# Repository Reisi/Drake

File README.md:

# Drake

The Drake hardware is a multi-purpose PCB which can be used to build a wireless dropper post actuator or a rear light.

## Actuator

### Features

- Bluetooth connectivity for remote control and configuration.
- I2C connectivity for control, configuration and sensor readings.
- construction files for Fox Transfer dropper posts available

## Light

### Features

- two configurations with either 16 or 44 WS2812 LEDs
- 8 configurable modes
- configurable LED pattern
- ability to control a dropper actuator over a FFC (using I2C)

## Firmware

Drake is part of The Helen Project. The source code and compiled firmware files are available [here](https://github.com/Reisi/The_Helen_Project/tree/master/Firmware/Helen/boards/Drake_10)

## License

This project is licensed under the BSD-2-clause License - see the [license.txt](license.txt) file for details

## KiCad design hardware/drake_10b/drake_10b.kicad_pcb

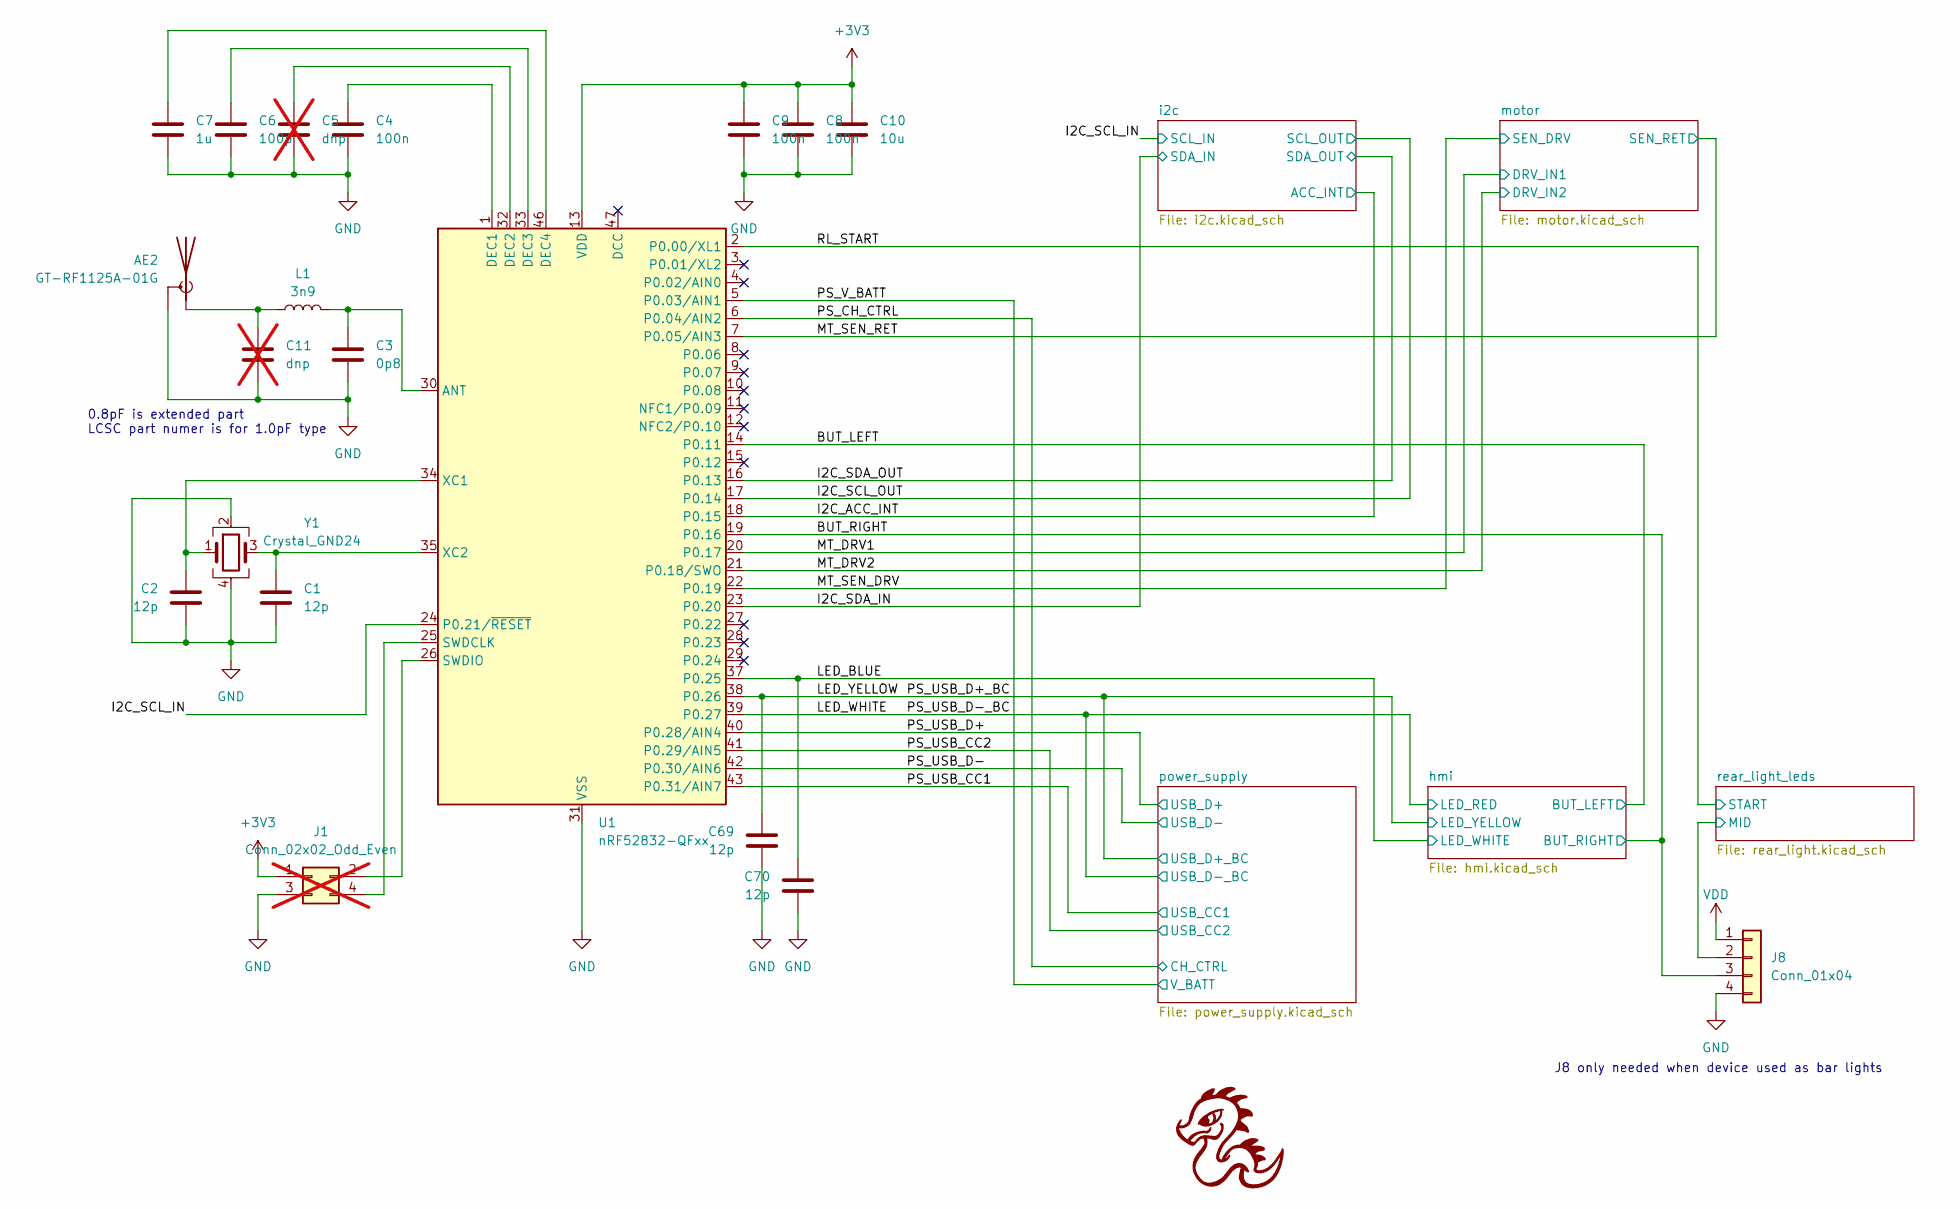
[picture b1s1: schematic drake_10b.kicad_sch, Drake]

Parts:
AE2: GT-RF1125A-01G; U.FL_Hirose_U.FL-R-SMT-1_Vertical; JLC SMD
C1, C2, C69, C70: 12p; C_0402_1005Metric; JLC 0402
C3: 0p8; C_0402_1005Metric; JLC 0402
C4, C8, C9: 100n; C_0402_1005Metric; JLC 0402
C5, C11: dnp; C_0402_1005Metric; not fitted
C6: 100p; C_0402_1005Metric; JLC 0402
C7: 1u; C_0402_1005Metric; JLC 0402
C10: 10u; C_0603_1608Metric; JLC 0603
J1: Conn_02x02_Odd_Even; PinHeader_2x02_P1.27mm_Vertical; not fitted
J8: Conn_01x04; Jushuo_AFC01-S04FCC-00_1x04-1MP_P0.50_Horizontal; JLC SMD,P=0.5mm
L1: 3n9; L_0402_1005Metric; JLC 0402
U1: nRF52832-QFxx; QFN-48-1EP_6x6mm_P0.4mm_EP4.6x4.6mm; JLC QFN-48-EP(6x6)
Y1: Crystal_GND24; Crystal_SMD_2016-4Pin_2.0x1.6mm; JLC SMD2016-4P

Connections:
+3V3: C8.1, C9.1, C10.1, J1.1, U1.13 (VDD), U1.36 (VDD), U1.48 (VDD); also elsewhere on the board
/BUT_LEFT: U1.14 (P0.11); also elsewhere on the board
/BUT_RIGHT: J8.3, U1.19 (P0.16); also elsewhere on the board
/I2C_ACC_INT: U1.18 (P0.15); also elsewhere on the board
/I2C_SCL_IN: U1.24 (P0.21/~RESET); also elsewhere on the board
/I2C_SCL_OUT: U1.17 (P0.14); also elsewhere on the board
/I2C_SDA_IN: U1.23 (P0.20); also elsewhere on the board
/I2C_SDA_OUT: U1.16 (P0.13); also elsewhere on the board
/LED_BLUE: C70.1, U1.37 (P0.25); also elsewhere on the board
/LED_WHITE: U1.39 (P0.27); also elsewhere on the board
/LED_YELLOW: C69.1, U1.38 (P0.26); also elsewhere on the board
/MT_DRV1: U1.20 (P0.17); also elsewhere on the board
/MT_DRV2: U1.21 (P0.18/SWO); also elsewhere on the board
/MT_SEN_DRV: U1.22 (P0.19); also elsewhere on the board
/MT_SEN_RET: U1.7 (P0.05/AIN3); also elsewhere on the board
/PS_CH_CTRL: U1.6 (P0.04/AIN2); also elsewhere on the board
/PS_USB_CC1: U1.43 (P0.31/AIN7); also elsewhere on the board
/PS_USB_CC2: U1.41 (P0.29/AIN5); also elsewhere on the board
/PS_USB_D+: U1.40 (P0.28/AIN4); also elsewhere on the board
/PS_USB_D-: U1.42 (P0.30/AIN6); also elsewhere on the board
/PS_V_BATT: U1.5 (P0.03/AIN1); also elsewhere on the board
/RL_START: U1.2 (P0.00/XL1); also elsewhere on the board
/rear_light_leds/MID: J8.2; also elsewhere on the board
GND: AE2.2 (Shield), C1.2, C2.2, C3.2, C4.2, C5.2, C6.2, C7.2, C8.2, C9.2, C10.2, C11.2, C69.2, C70.2, J1.3, J8.4, U1.31 (VSS), U1.45 (VSS), U1.49 (VSS), Y1.2, Y1.4; also elsewhere on the board
unnamed: AE2.1 (A), C11.1, L1.1
unnamed: J1.2, U1.26 (SWDIO)
unnamed: J1.4, U1.25 (SWDCLK)
unnamed: C3.1, L1.2, U1.30 (ANT)
unnamed: C4.1, U1.1 (DEC1)
unnamed: C5.1, U1.32 (DEC2)
unnamed: C6.1, U1.33 (DEC3)
unnamed: C7.1, U1.46 (DEC4)
unnamed: C2.1, U1.34 (XC1), Y1.1
unnamed: C1.1, U1.35 (XC2), Y1.3
VDD: J8.1; also elsewhere on the board

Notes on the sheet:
J8 only needed when device used as bar lights
0.8pF is extended part LCSC part numer is for 1.0pF type

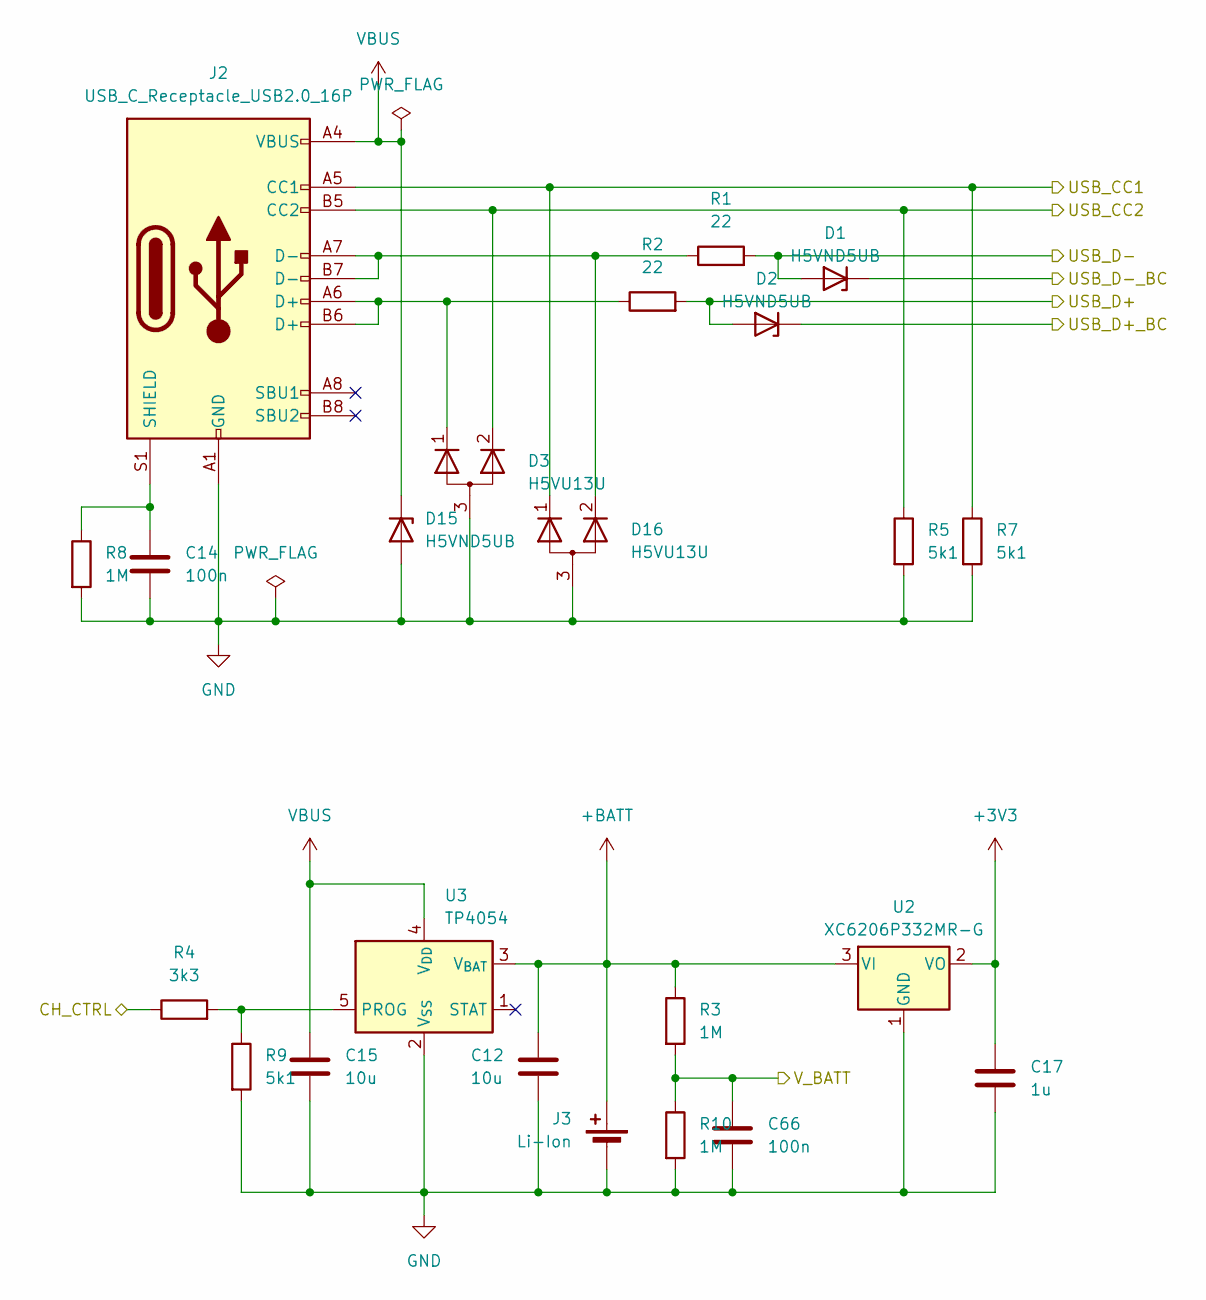
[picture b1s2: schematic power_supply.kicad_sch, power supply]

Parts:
C12, C15: 10u; C_0603_1608Metric; JLC 0603
C14, C66: 100n; C_0402_1005Metric; JLC 0402
C17: 1u; C_0402_1005Metric; JLC 0402
D1, D2, D15: H5VND5UB; D_SOD-523; JLC SOD-523
D3, D16: H5VU13U; Diodes_DFN1006-3; JLC DFN1006-3L
J2: USB_C_Receptacle_USB2.0_16P; USB_C_Receptacle_XKB_U262-16XN-4BVC11; JLC SMD
J3: Li-Ion; JST_PH_B2B-PH-K_1x02_P2.00mm_Vertical; JLC Plugin,P=2mm
R1, R2: 22; R_0402_1005Metric; JLC 0402
R3, R8, R10: 1M; R_0402_1005Metric; JLC 0402
R4: 3k3; R_0402_1005Metric; JLC 0402
R5, R7, R9: 5k1; R_0402_1005Metric; JLC 0402
U2: XC6206P332MR-G; SOT-23-3; JLC SOT-23-3L
U3: TP4054; SOT-23-5; LCSC C32574

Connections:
+3V3: C17.1, U2.2 (VO); also elsewhere on the board
+BATT: C12.1, J3.2 (+), R3.1, U2.3 (VI), U3.3 (V_{BAT}); also elsewhere on the board
/LED_WHITE: D1.1 (K); also elsewhere on the board
/LED_YELLOW: D2.1 (K); also elsewhere on the board
/PS_CH_CTRL: R4.1; also elsewhere on the board
/PS_USB_CC1: D16.1 (K), J2.A5 (CC1), R7.1; also elsewhere on the board
/PS_USB_CC2: D3.2 (K), J2.B5 (CC2), R5.1; also elsewhere on the board
/PS_USB_D+: D2.2 (A), R2.2; also elsewhere on the board
/PS_USB_D-: D1.2 (A), R1.2; also elsewhere on the board
/PS_V_BATT: C66.1, R3.2, R10.1; also elsewhere on the board
GND: C12.2, C14.2, C15.2, C17.2, C66.2, D3.3 (A), D15.2 (A), D16.3 (A), J2.A1 (GND), J2.A12 (GND), J2.B1 (GND), J2.B12 (GND), J3.1 (-), R5.2, R7.2, R8.2, R9.2, R10.2, U2.1 (GND), U3.2 (V_{SS}); also elsewhere on the board
unnamed: D3.1 (K), J2.A6 (D+), J2.B6 (D+), R2.1
unnamed: D16.2 (K), J2.A7 (D-), J2.B7 (D-), R1.1
unnamed: C14.1, J2.S1 (SHIELD), R8.1
unnamed: R4.2, R9.1, U3.5 (PROG)
VBUS: C15.1, D15.1 (K), J2.A4 (VBUS), J2.A9 (VBUS), J2.B4 (VBUS), J2.B9 (VBUS), U3.4 (V_{DD})

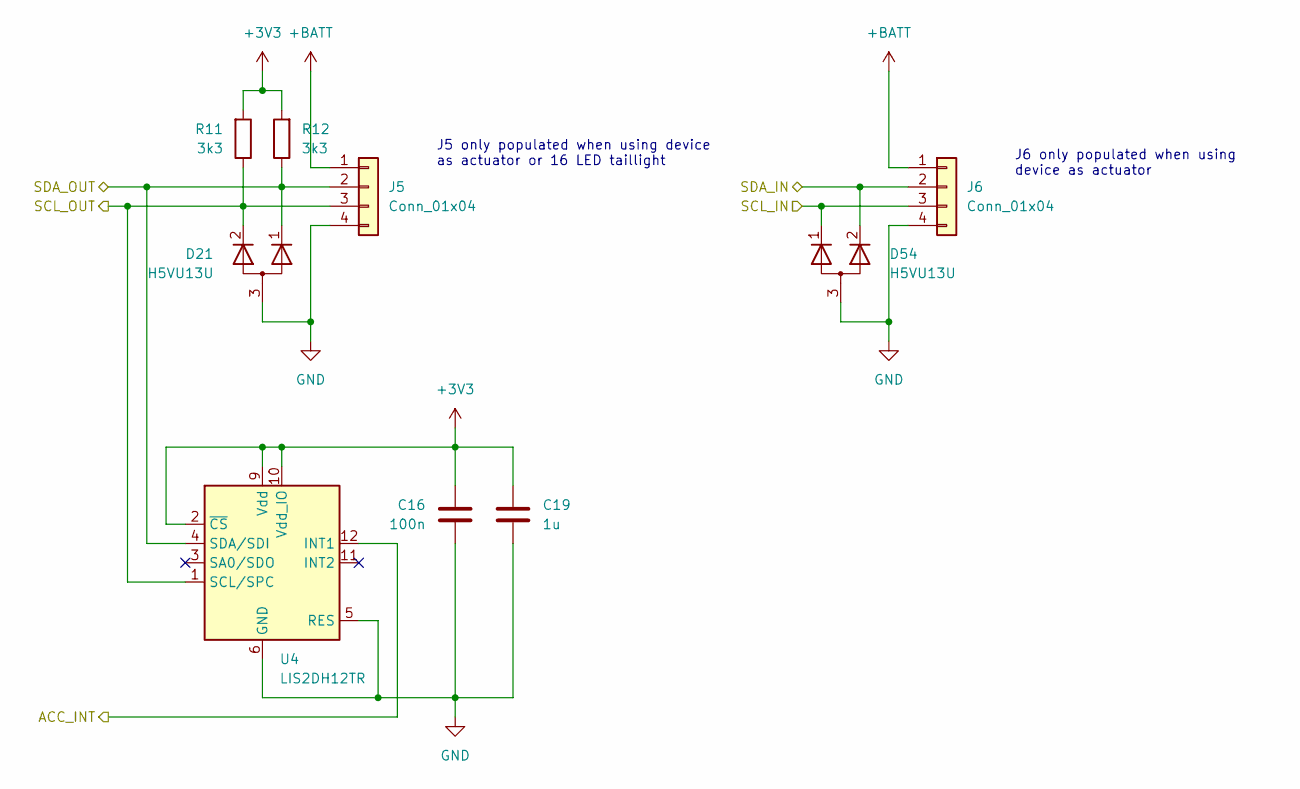
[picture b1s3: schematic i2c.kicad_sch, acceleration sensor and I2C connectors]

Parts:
C16: 100n; C_0402_1005Metric; JLC 0402
C19: 1u; C_0402_1005Metric; JLC 0402
D21, D54: H5VU13U; Diodes_DFN1006-3; JLC DFN1006-3L
J5, J6: Conn_01x04; Jushuo_AFC01-S04FCC-00_1x04-1MP_P0.50_Horizontal; JLC SMD,P=0.5mm
R11, R12: 3k3; R_0402_1005Metric; JLC 0402
U4: LIS2DH12TR; LGA-12_2x2mm_P0.5mm; JLC LGA-12

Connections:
+3V3: C16.1, C19.1, R11.2, R12.2, U4.2 (~CS), U4.9 (Vdd), U4.10 (Vdd_IO); also elsewhere on the board
+BATT: J5.1, J6.1; also elsewhere on the board
/I2C_ACC_INT: U4.12 (INT1); also elsewhere on the board
/I2C_SCL_IN: D54.1 (K), J6.3; also elsewhere on the board
/I2C_SCL_OUT: D21.2 (K), J5.3, R11.1, U4.1 (SCL/SPC); also elsewhere on the board
/I2C_SDA_IN: D54.2 (K), J6.2; also elsewhere on the board
/I2C_SDA_OUT: D21.1 (K), J5.2, R12.1, U4.4 (SDA/SDI); also elsewhere on the board
GND: C16.2, C19.2, D21.3 (A), D54.3 (A), J5.4, J6.4, U4.5 (RES), U4.6 (GND), U4.7 (GND), U4.8 (GND); also elsewhere on the board

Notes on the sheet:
J6 only populated when using device as actuator
J5 only populated when using device as actuator or 16 LED taillight

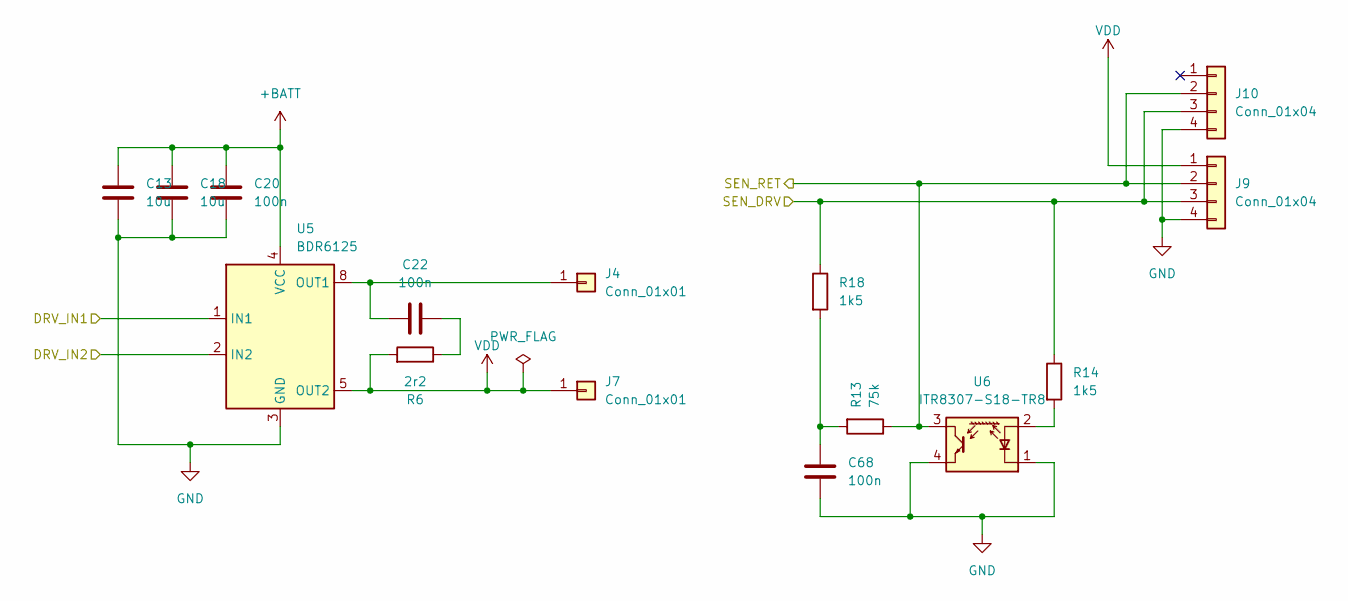
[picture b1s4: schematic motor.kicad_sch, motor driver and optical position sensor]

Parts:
C13, C18: 10u; C_0603_1608Metric; JLC 0603
C20, C68: 100n; C_0402_1005Metric; JLC 0402
C22: 100n; C_0603_1608Metric; JLC 0603
J4, J7: Conn_01x01; PinHeader_1x01_P2.00mm_Vertical
J9, J10: Conn_01x04; FFC_SolderCon_4pin_3,5x0,3mm_Pitch0.5mm; JLC SMD,P=0.5mm
R6: 2r2; R_0603_1608Metric; JLC 0603
R13: 75k; R_0402_1005Metric; JLC 0402
R14, R18: 1k5; R_0402_1005Metric; JLC 0402
U5: BDR6125; SOIC-8_3.9x4.9mm_P1.27mm
U6: ITR8307-S18-TR8; Everlight_ITR1201SR10AR; JLC SMD

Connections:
+BATT: C13.1, C18.1, C20.1, U5.4 (VCC); also elsewhere on the board
/MT_DRV1: U5.1 (IN1); also elsewhere on the board
/MT_DRV2: U5.2 (IN2); also elsewhere on the board
/MT_SEN_DRV: J9.3, J10.3, R14.1, R18.1; also elsewhere on the board
/MT_SEN_RET: J9.2, J10.2, R13.1, U6.3; also elsewhere on the board
GND: C13.2, C18.2, C20.2, C68.2, J9.4, J10.4, U5.3 (GND), U6.1 (K), U6.4; also elsewhere on the board
unnamed: C22.1, R6.1
unnamed: C68.1, R13.2, R18.2
unnamed: C22.2, J4.1, U5.7 (OUT1), U5.8 (OUT1)
unnamed: R14.2, U6.2 (A)
VDD: J7.1, J9.1, R6.2, U5.5 (OUT2), U5.6 (OUT2); also elsewhere on the board

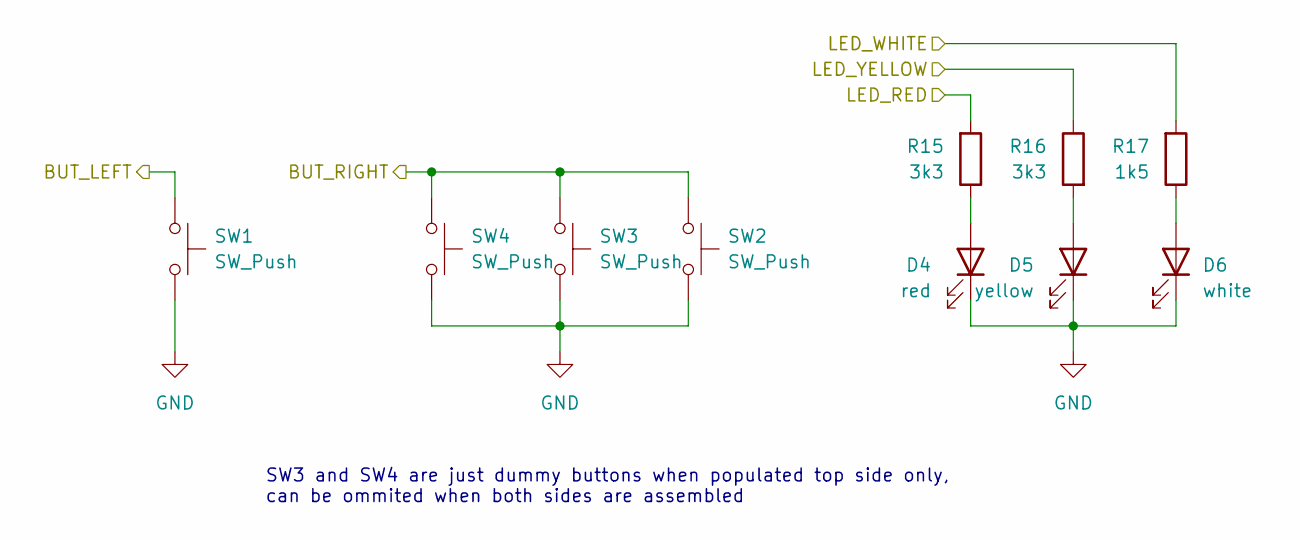
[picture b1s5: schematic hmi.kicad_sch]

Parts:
D4: red; LED_0603_1608Metric; JLC 0603
D5: yellow; LED_0603_1608Metric; JLC 0603
D6: white; LED_0603_1608Metric; LCSC C2290
R15, R16: 3k3; R_0402_1005Metric; JLC 0402
R17: 1k5; R_0402_1005Metric; JLC 0402
SW1, SW2, SW3, SW4: SW_Push; SW_Push_1P1T_XKB_TS-1187A; JLC SMD

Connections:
/BUT_LEFT: SW1.1; also elsewhere on the board
/BUT_RIGHT: SW2.1, SW3.1, SW4.1; also elsewhere on the board
/LED_BLUE: R17.2; also elsewhere on the board
/LED_WHITE: R15.2; also elsewhere on the board
/LED_YELLOW: R16.1; also elsewhere on the board
GND: D4.1 (K), D5.1 (K), D6.1 (K), SW1.2, SW2.2, SW3.2, SW4.2; also elsewhere on the board
unnamed: D4.2 (A), R15.1
unnamed: D5.2 (A), R16.2
unnamed: D6.2 (A), R17.1

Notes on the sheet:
SW3 and SW4 are just dummy buttons when populated top side only, can be ommited when both sides are assembled

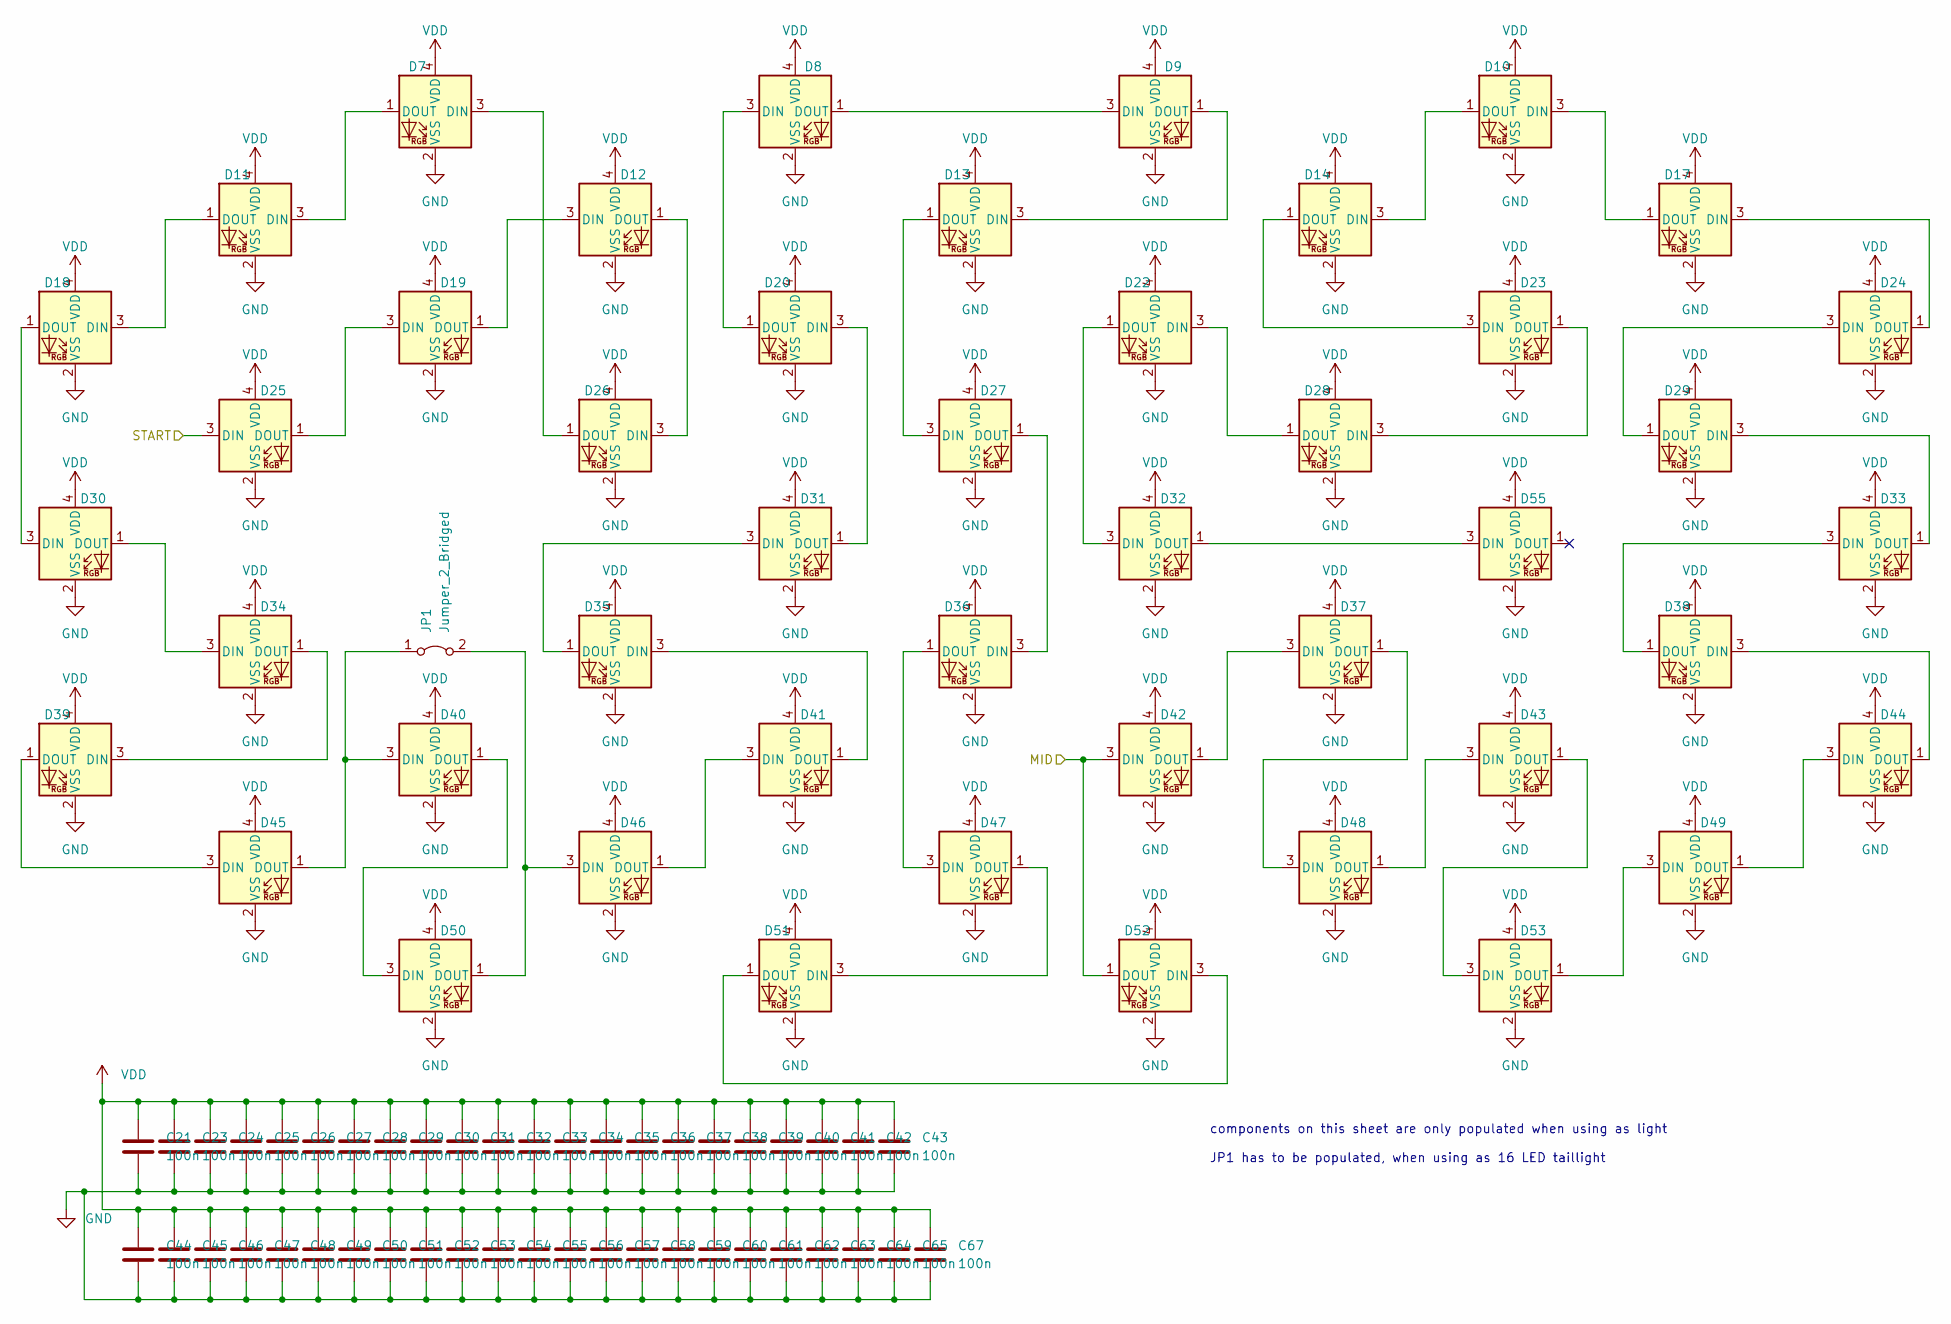
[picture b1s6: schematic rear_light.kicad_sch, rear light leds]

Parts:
C21, C23, C24, C25, C26, C27, C28, C29, C30, C31, C32, C33, C34, C35, C36, C37, C38, C39, C40, C41, C42, C43, C44, C45, C46, C47, C48, C49, C50, C51, C52, C53, C54, C55, C56, C57, C58, C59, C60, C61, C62, C63, C64, C65, C67: 100n; C_0603_1608Metric; JLC 0603
D7, D8, D9, D10, D11, D12, D13, D14, D17, D18, D19, D20, D22, D23, D24, D25, D26, D27, D28, D29, D30, D31, D32, D33, D34, D35, D36, D37, D38, D39, D40, D41, D42, D43, D44, D45, D46, D47, D48, D49, D50, D51, D52, D53, D55: WS2812B-2020; LED_WS2812B-2020_PLCC4_2.0x2.0mm; JLC SMS,2x2mm
JP1: Jumper_2_Bridged; R_0402_1005Metric; JLC 0402

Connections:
/RL_START: D25.3 (DIN); also elsewhere on the board
/rear_light_leds/MID: D42.3 (DIN), D52.1 (DOUT); also elsewhere on the board
GND: C21.2, C23.2, C24.2, C25.2, C26.2, C27.2, C28.2, C29.2, C30.2, C31.2, C32.2, C33.2, C34.2, C35.2, C36.2, C37.2, C38.2, C39.2, C40.2, C41.2, C42.2, C43.2, C44.2, C45.2, C46.2, C47.2, C48.2, C49.2, C50.2, C51.2, C52.2, C53.2, C54.2, C55.2, C56.2, C57.2, C58.2, C59.2, C60.2, C61.2, C62.2, C63.2, C64.2, C65.2, C67.2, D7.2 (VSS), D8.2 (VSS), D9.2 (VSS), D10.2 (VSS), D11.2 (VSS), D12.2 (VSS), D13.2 (VSS), D14.2 (VSS), D17.2 (VSS), D18.2 (VSS), D19.2 (VSS), D20.2 (VSS), D22.2 (VSS), D23.2 (VSS), D24.2 (VSS), D25.2 (VSS), D26.2 (VSS), D27.2 (VSS), D28.2 (VSS), D29.2 (VSS), D30.2 (VSS), D31.2 (VSS), D32.2 (VSS), D33.2 (VSS), D34.2 (VSS), D35.2 (VSS), D36.2 (VSS), D37.2 (VSS), D38.2 (VSS), D39.2 (VSS), D40.2 (VSS), D41.2 (VSS), D42.2 (VSS), D43.2 (VSS), D44.2 (VSS), D45.2 (VSS), D46.2 (VSS), D47.2 (VSS), D48.2 (VSS), D49.2 (VSS), D50.2 (VSS), D51.2 (VSS), D52.2 (VSS), D53.2 (VSS), D55.2 (VSS); also elsewhere on the board
unnamed: D8.1 (DOUT), D9.3 (DIN)
unnamed: D10.3 (DIN), D17.1 (DOUT)
unnamed: D10.1 (DOUT), D14.3 (DIN)
unnamed: D7.1 (DOUT), D11.3 (DIN)
unnamed: D11.1 (DOUT), D18.3 (DIN)
unnamed: D12.3 (DIN), D19.1 (DOUT)
unnamed: D12.1 (DOUT), D26.3 (DIN)
unnamed: D9.1 (DOUT), D13.3 (DIN)
unnamed: D13.1 (DOUT), D27.3 (DIN)
unnamed: D14.1 (DOUT), D23.3 (DIN)
unnamed: D17.3 (DIN), D24.1 (DOUT)
unnamed: D18.1 (DOUT), D30.3 (DIN)
unnamed: D19.3 (DIN), D25.1 (DOUT)
unnamed: D20.3 (DIN), D31.1 (DOUT)
unnamed: D8.3 (DIN), D20.1 (DOUT)
unnamed: D22.3 (DIN), D28.1 (DOUT)
unnamed: D22.1 (DOUT), D32.3 (DIN)
unnamed: D23.1 (DOUT), D28.3 (DIN)
unnamed: D24.3 (DIN), D29.1 (DOUT)
unnamed: D7.3 (DIN), D26.1 (DOUT)
unnamed: D27.1 (DOUT), D36.3 (DIN)
unnamed: D29.3 (DIN), D33.1 (DOUT)
unnamed: D30.1 (DOUT), D34.3 (DIN)
unnamed: D31.3 (DIN), D35.1 (DOUT)
unnamed: D32.1 (DOUT), D55.3 (DIN)
unnamed: D33.3 (DIN), D38.1 (DOUT)
unnamed: D34.1 (DOUT), D39.3 (DIN)
unnamed: D35.3 (DIN), D41.1 (DOUT)
unnamed: D36.1 (DOUT), D47.3 (DIN)
unnamed: D37.3 (DIN), D42.1 (DOUT)
unnamed: D37.1 (DOUT), D48.3 (DIN)
unnamed: D38.3 (DIN), D44.1 (DOUT)
unnamed: D39.1 (DOUT), D45.3 (DIN)
unnamed: D40.3 (DIN), D45.1 (DOUT), JP1.1 (A)
unnamed: D40.1 (DOUT), D50.3 (DIN)
unnamed: D41.3 (DIN), D46.1 (DOUT)
unnamed: D43.3 (DIN), D48.1 (DOUT)
unnamed: D43.1 (DOUT), D53.3 (DIN)
unnamed: D44.3 (DIN), D49.1 (DOUT)
unnamed: D46.3 (DIN), D50.1 (DOUT), JP1.2 (B)
unnamed: D47.1 (DOUT), D51.3 (DIN)
unnamed: D49.3 (DIN), D53.1 (DOUT)
unnamed: D51.1 (DOUT), D52.3 (DIN)
VDD: C21.1, C23.1, C24.1, C25.1, C26.1, C27.1, C28.1, C29.1, C30.1, C31.1, C32.1, C33.1, C34.1, C35.1, C36.1, C37.1, C38.1, C39.1, C40.1, C41.1, C42.1, C43.1, C44.1, C45.1, C46.1, C47.1, C48.1, C49.1, C50.1, C51.1, C52.1, C53.1, C54.1, C55.1, C56.1, C57.1, C58.1, C59.1, C60.1, C61.1, C62.1, C63.1, C64.1, C65.1, C67.1, D7.4 (VDD), D8.4 (VDD), D9.4 (VDD), D10.4 (VDD), D11.4 (VDD), D12.4 (VDD), D13.4 (VDD), D14.4 (VDD), D17.4 (VDD), D18.4 (VDD), D19.4 (VDD), D20.4 (VDD), D22.4 (VDD), D23.4 (VDD), D24.4 (VDD), D25.4 (VDD), D26.4 (VDD), D27.4 (VDD), D28.4 (VDD), D29.4 (VDD), D30.4 (VDD), D31.4 (VDD), D32.4 (VDD), D33.4 (VDD), D34.4 (VDD), D35.4 (VDD), D36.4 (VDD), D37.4 (VDD), D38.4 (VDD), D39.4 (VDD), D40.4 (VDD), D41.4 (VDD), D42.4 (VDD), D43.4 (VDD), D44.4 (VDD), D45.4 (VDD), D46.4 (VDD), D47.4 (VDD), D48.4 (VDD), D49.4 (VDD), D50.4 (VDD), D51.4 (VDD), D52.4 (VDD), D53.4 (VDD), D55.4 (VDD); also elsewhere on the board

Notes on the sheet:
components on this sheet are only populated when using as light JP1 has to be populated, when using as 16 LED taillight

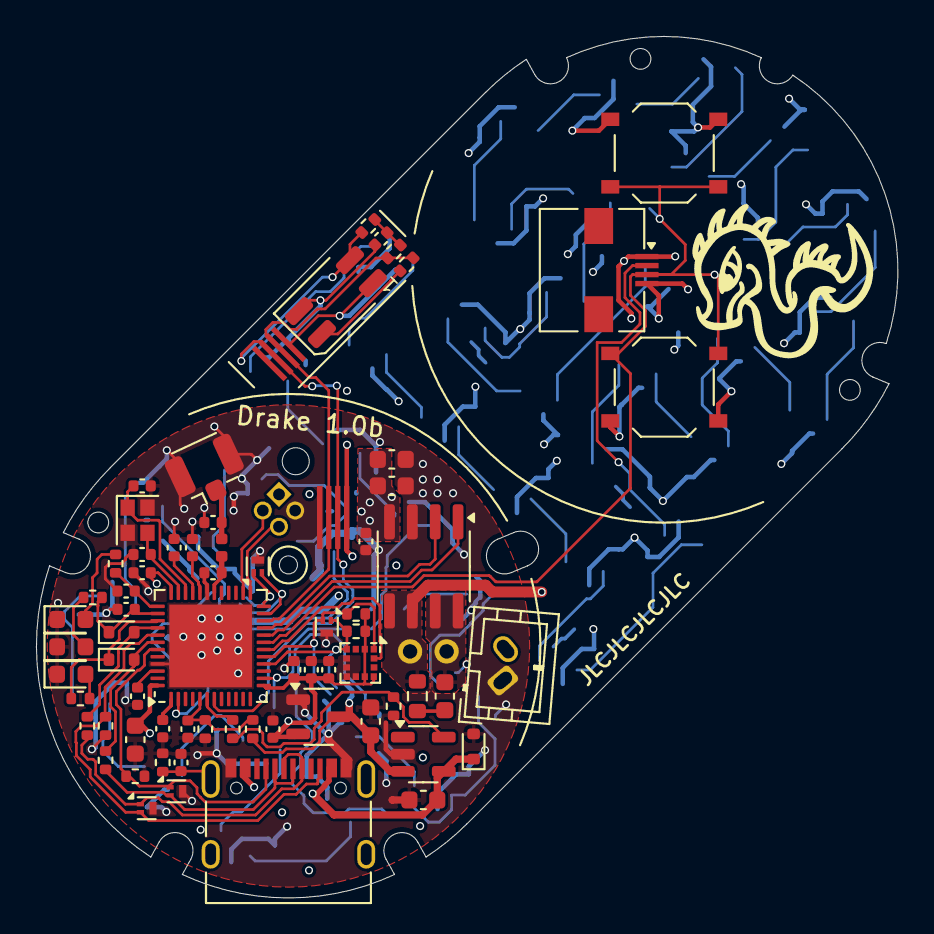
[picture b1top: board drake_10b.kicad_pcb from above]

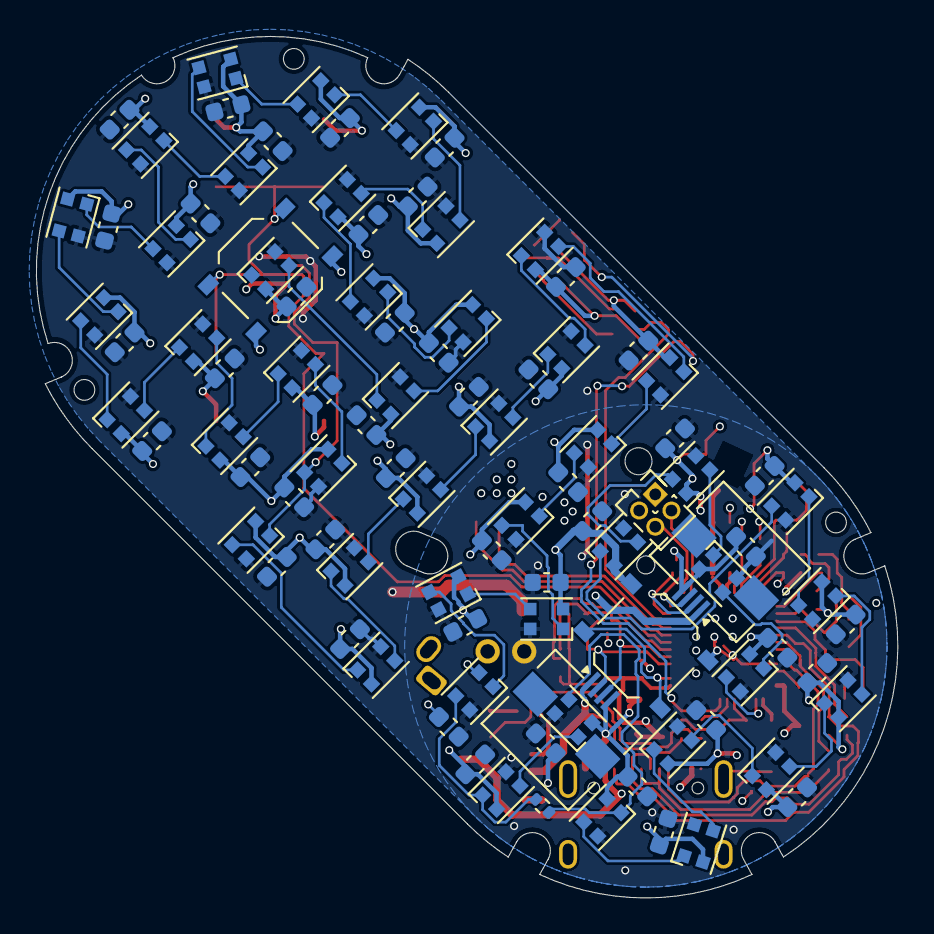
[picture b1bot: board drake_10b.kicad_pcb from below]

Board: 4 copper layers, 47.9 x 47.9 mm, 167 parts (96 on the bottom side), 91 nets.

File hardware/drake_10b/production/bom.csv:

Designator,Footprint,Quantity,Value,LCSC Part #
AE2,U.FL_Hirose_U.FL-R-SMT-1_Vertical,1,GT-RF1125A-01G,C5299419
"C1, C2, C69, C70",0402,4,12p,C1547
"C10, C12, C13, C15, C18",0603,5,10u,C19702
"C14, C16, C20, C4, C66, C68, C8, C9",0402,8,100n,C307331
"C17, C19, C7",0402,3,1u,C52923
"C21, C22, C23, C24, C25, C26, C27, C28, C29, C30, C31, C32, C33, C34, C35, C36, C37, C38, C39, C40, C41, C42, C43, C44, C45, C46, C47, C48, C49, C50, C51, C52, C53, C54, C55, C56, C57, C58, C59, C60, C61, C62, C63, C64, C65, C67",0603,46,100n,C14663
C3,0402,1,0p8,C1550
C6,0402,1,100p,C1546
"D1, D15, D2",D_SOD-523,3,H5VND5UB,C20615819
"D10, D11, D12, D13, D14, D17, D18, D19, D20, D22, D23, D24, D25, D26, D27, D28, D29, D30, D31, D32, D33, D34, D35, D36, D37, D38, D39, D40, D41, D42, D43, D44, D45, D46, D47, D48, D49, D50, D51, D52, D53, D55, D7, D8, D9",LED_WS2812B-2020_PLCC4_2.0x2.0mm,45,WS2812B-2020,C2976072
"D16, D21, D3, D54",Diodes_DFN1006-3,4,H5VU13U,C20615795
D4,0603,1,red,C2286
D5,0603,1,yellow,C89811
D6,0603,1,white,C2290
J2,USB_C_Receptacle_XKB_U262-16XN-4BVC11,1,USB_C_Receptacle_USB2.0_16P,C2931474
J3,JST_PH_B2B-PH-K_1x02_P2.00mm_Vertical,1,Li-Ion,C131337
"J5, J6, J8",Jushuo_AFC01-S04FCC-00_1x04-1MP_P0.50_Horizontal,3,Conn_01x04,C262260
JP1,0402,1,Jumper_2_Bridged,C17168
L1,0402,1,3n9,C14033
"R1, R2",0402,2,22,C25092
"R10, R3, R8",0402,3,1M,C26083
"R11, R12, R15, R16, R4",0402,5,3k3,C25890
R13,0402,1,75k,C25798
"R14, R17, R18",0402,3,1k5,C25867
"R5, R7, R9",0402,3,5k1,C25905
R6,0603,1,2r2,C22939
"SW1, SW2, SW3, SW4",SW_Push_1P1T_XKB_TS-1187A,4,SW_Push,C318884
U1,QFN-48-1EP_6x6mm_P0.4mm_EP4.6x4.6mm,1,nRF52832-QFxx,C77540
U2,SOT-23-3,1,XC6206P332MR-G,C5446
U3,SOT-23-5,1,TP4054,C32574
U4,LGA-12_2x2mm_P0.5mm,1,LIS2DH12TR,C110926
U5,SOIC-8_3.9x4.9mm_P1.27mm,1,BDR6125,
U6,Everlight_ITR1201SR10AR,1,ITR8307-S18-TR8,C409524
Y1,Crystal_SMD_2016-4Pin_2.0x1.6mm,1,Crystal_GND24,C2965584

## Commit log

2025-06-22 added step file
2025-07-02 modified thread and gearbox
2025-07-02 revised production files
